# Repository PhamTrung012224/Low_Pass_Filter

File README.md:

# Low_Pass_Filter
This repository content schematic file using Qucs-s and PCB file using KiCAD EDA
10kHZ Low Pass Filter

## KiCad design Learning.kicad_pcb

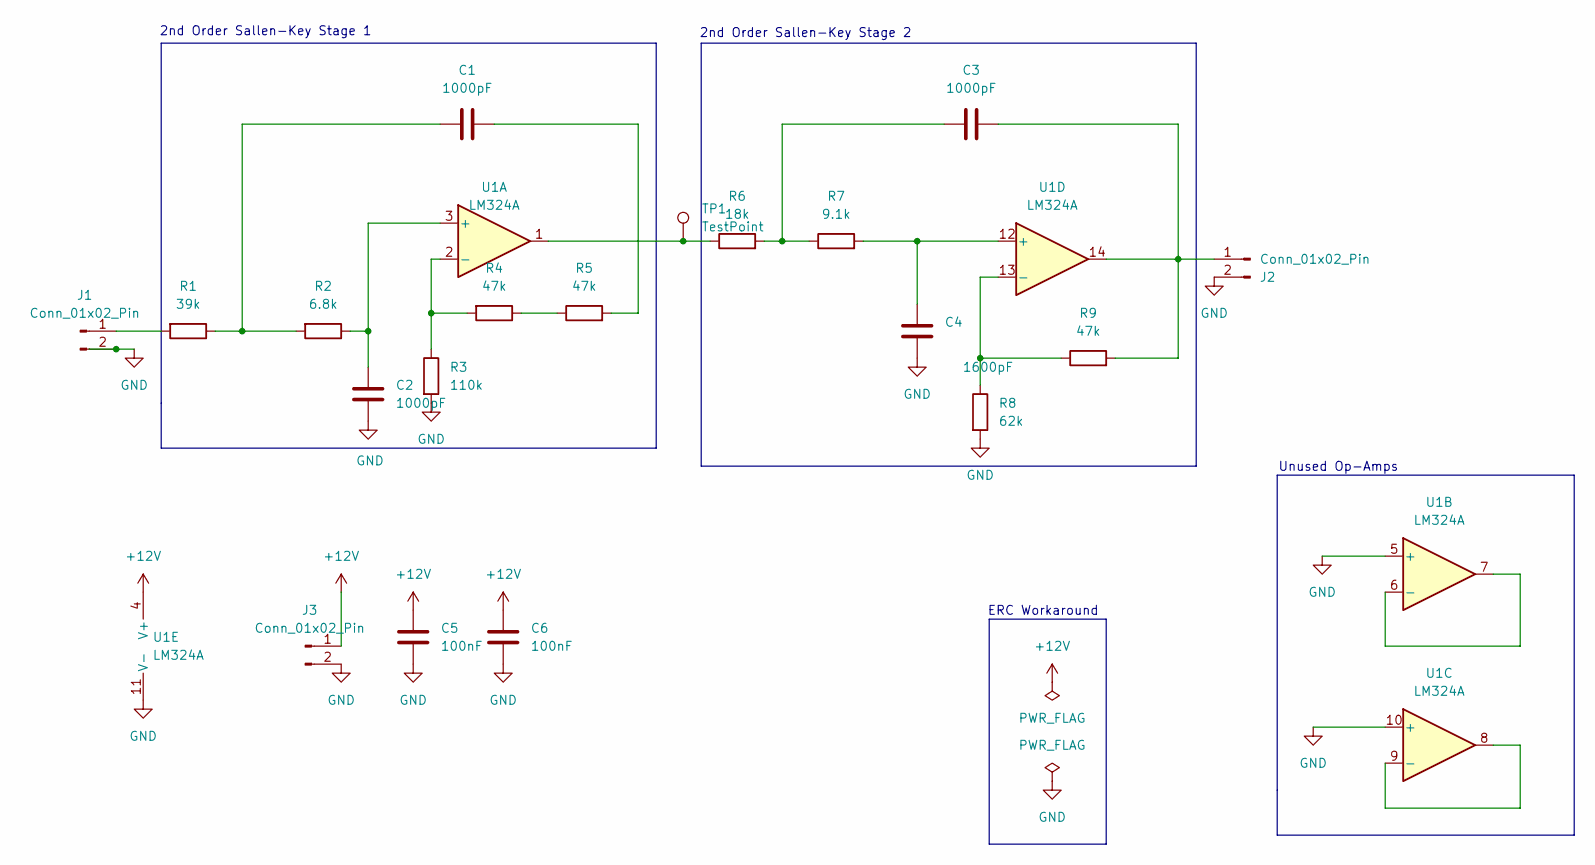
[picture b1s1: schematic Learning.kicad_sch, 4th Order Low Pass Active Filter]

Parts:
C1, C2, C3: 1000pF; C_0603_1608Metric_Pad1.08x0.95mm_HandSolder
C4: 1600pF; C_0603_1608Metric_Pad1.08x0.95mm_HandSolder
C5, C6: 100nF; C_1206_3216Metric
J1, J2, J3: Conn_01x02_Pin; PinHeader_1x02_P2.54mm_Vertical
R1: 39k; R_0603_1608Metric
R2: 6.8k; R_0603_1608Metric
R3: 110k; R_0603_1608Metric
R4, R5, R9: 47k; R_0603_1608Metric
R6: 18k; R_0603_1608Metric
R7: 9.1k; R_0603_1608Metric
R8: 62k; R_0603_1608Metric
TP1: TestPoint; TestPoint_Pad_2.0x2.0mm
U1: LM324A; DIP-14_W7.62mm

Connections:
+12V: C5.1, C6.1, J3.1, U1.4 (V+)
GND: C2.2, C4.1, C5.2, C6.2, J1.2, J2.2, J3.2, R3.2, R8.2, U1.5 (+), U1.10 (+), U1.11 (V-)
unnamed: C1.1, R1.1, R2.2
unnamed: C1.2, R5.2
unnamed: C3.1, R6.2, R7.1
unnamed: J1.1, R1.2
unnamed: C3.2, J2.1, R9.2, U1.14
unnamed: R4.1, R5.1
unnamed: R6.1, TP1.1, U1.1
unnamed: C2.1, R2.1, U1.3 (+)
unnamed: R3.1, R4.2, U1.2 (-)
unnamed: U1.6 (-), U1.7
unnamed: U1.8, U1.9 (-)
unnamed: C4.2, R7.2, U1.12 (+)
unnamed: R8.1, R9.1, U1.13 (-)

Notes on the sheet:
ERC Workaround
2nd Order Sallen-Key Stage 1
Unused Op-Amps
2nd Order Sallen-Key Stage 2

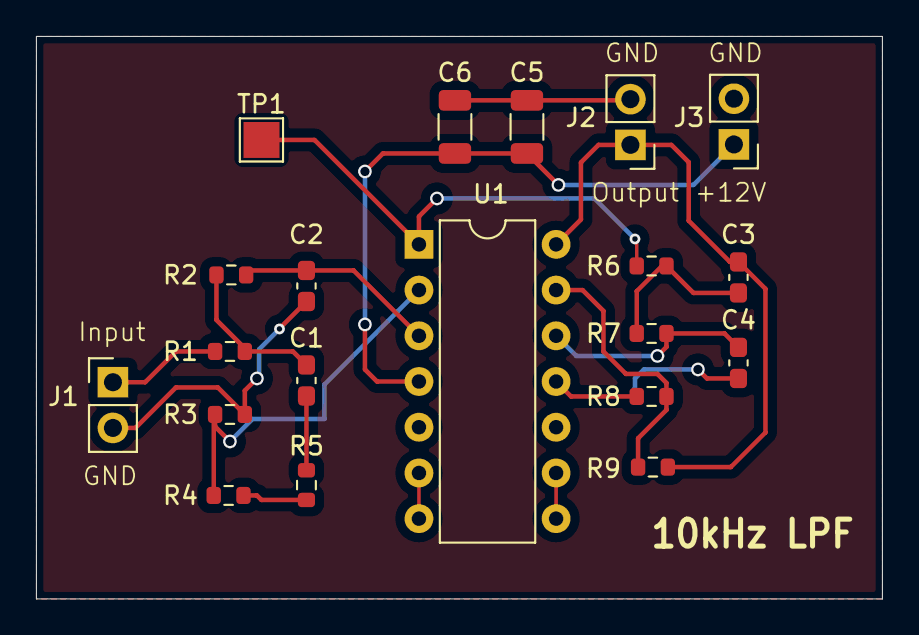
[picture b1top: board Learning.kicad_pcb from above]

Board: 2 copper layers, 47.0 x 31.2 mm, 20 parts (0 on the bottom side), 15 nets.

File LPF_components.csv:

Reference,Value,Datasheet,Footprint,Qty,DNP
"C1,C2,C3",1000pF,~,Capacitor_SMD:C_0603_1608Metric_Pad1.08x0.95mm_HandSolder,3,
C4,1600pF,~,Capacitor_SMD:C_0603_1608Metric_Pad1.08x0.95mm_HandSolder,1,
"C5,C6",100nF,~,Capacitor_SMD:C_1206_3216Metric,2,
"J1,J2,J3",Conn_01x02_Pin,~,Connector_PinHeader_2.54mm:PinHeader_1x02_P2.54mm_Vertical,3,
R1,39k,~,Resistor_SMD:R_0603_1608Metric,1,
R2,6.8k,~,Resistor_SMD:R_0603_1608Metric,1,
R3,110k,~,Resistor_SMD:R_0603_1608Metric,1,
"R4,R5,R9",47k,~,Resistor_SMD:R_0603_1608Metric,3,
R6,18k,~,Resistor_SMD:R_0603_1608Metric,1,
R7,9.1k,~,Resistor_SMD:R_0603_1608Metric,1,
R8,62k,~,Resistor_SMD:R_0603_1608Metric,1,
TP1,TestPoint,~,TestPoint:TestPoint_Pad_2.0x2.0mm,1,
U1,LM324A,http://www.ti.com/lit/ds/symlink/lm2902-n.pdf,Package_DIP:DIP-14_W7.62mm,1,

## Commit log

2024-04-09 Create low pass filter schematic with non standard value of components using Qucs-s tools
2024-04-09 Change non standard value to standard value
2024-04-09 create exel file content list of components
2024-04-09 Redraw Low Pass Filter Schematic using KiCAD tools to generate PCB
2024-04-09 Generate PCB Layout of Low Pass Filter Schematic
